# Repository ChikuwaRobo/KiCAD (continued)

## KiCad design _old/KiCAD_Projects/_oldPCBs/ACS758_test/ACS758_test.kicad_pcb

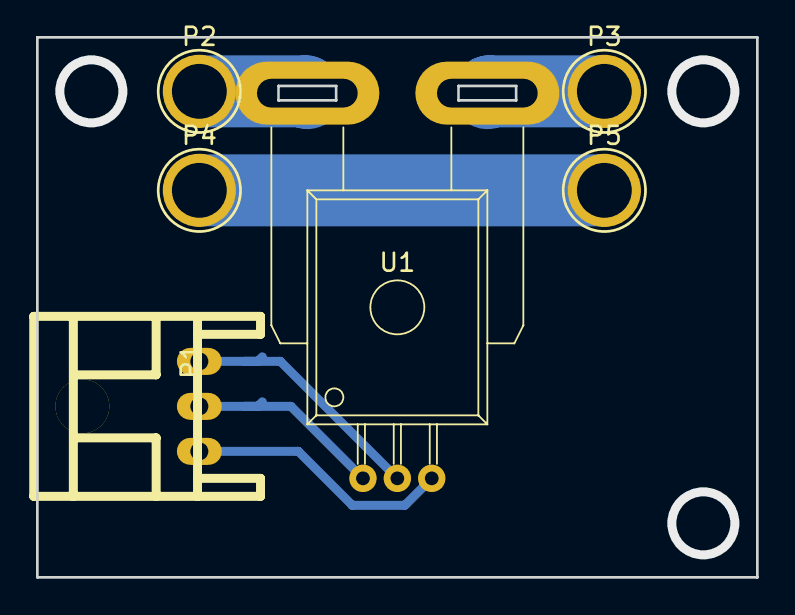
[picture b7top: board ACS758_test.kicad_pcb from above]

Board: 2 copper layers, 40.0 x 30.0 mm, 7 parts (1 on the bottom side), 6 nets.

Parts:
C1: C; C2012
P1: CONN_01X03; XA_3LC
P2, P3, P4, P5: CONN_01X01; 1pin
U1: ACS758; ACS785xCB

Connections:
unnamed: C1.1, P1.1, U1.2
unnamed: C1.2, P1.2, U1.1
unnamed: P1.3, U1.3
unnamed: P2.1, U1.5
unnamed: P3.1, U1.4
unnamed: P4.1, P5.1
